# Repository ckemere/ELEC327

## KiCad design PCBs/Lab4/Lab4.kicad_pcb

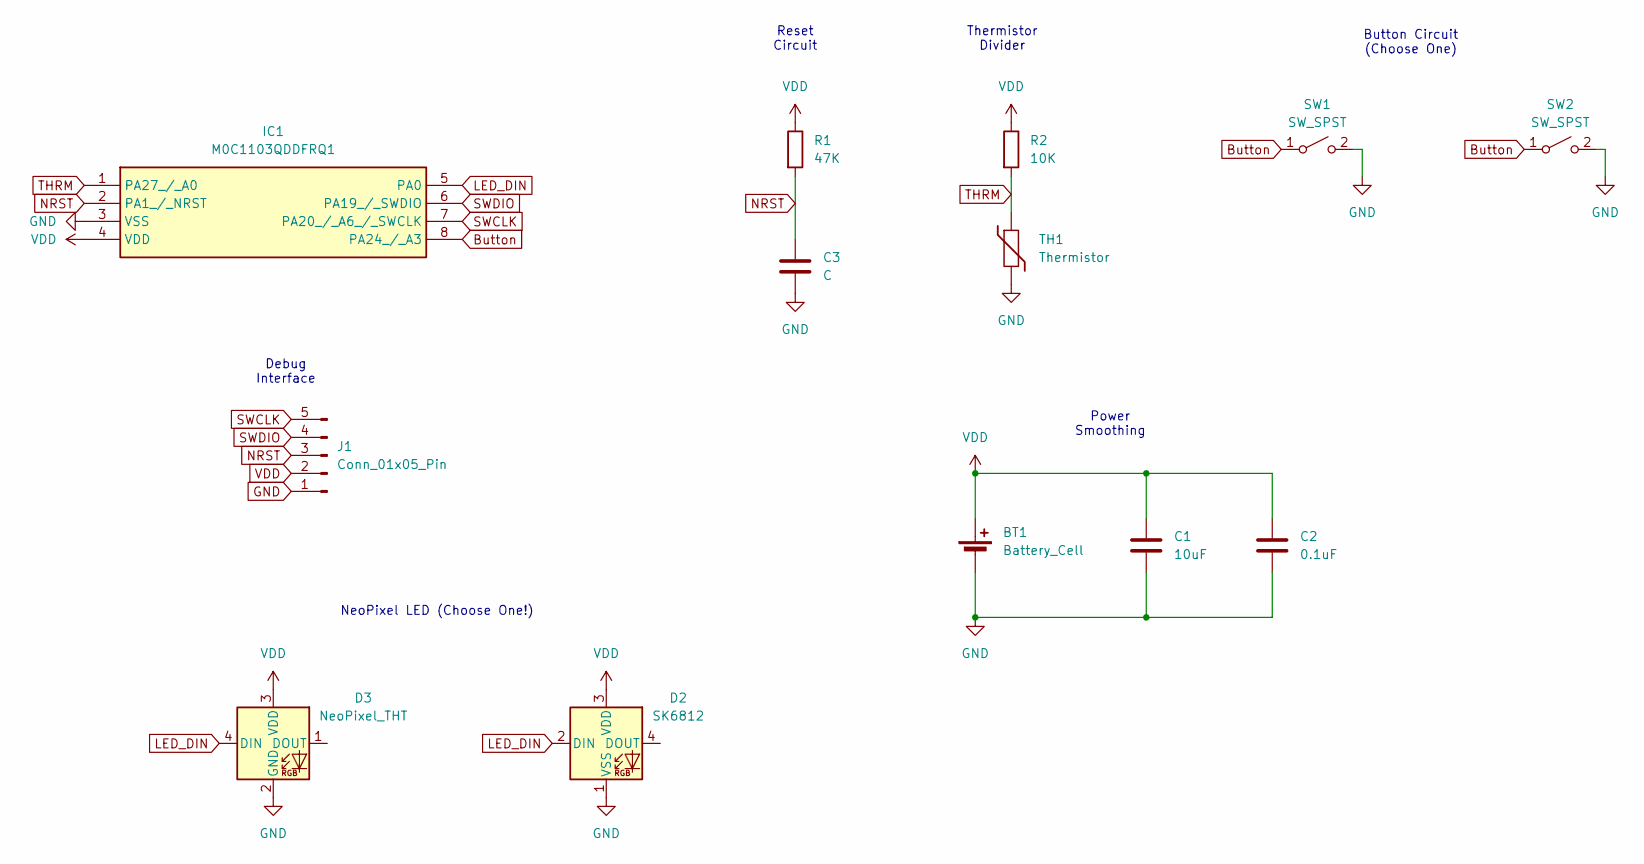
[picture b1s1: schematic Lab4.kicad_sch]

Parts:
BT1: Battery_Cell; BatteryHolder_Keystone_3001_1x12mm
C1: 10uF; C_1206_3216Metric_Pad1.33x1.80mm_HandSolder
C2: 0.1uF; C_1206_3216Metric_Pad1.33x1.80mm_HandSolder
C3: C; C_1206_3216Metric_Pad1.33x1.80mm_HandSolder
D2: SK6812; LED_SK6812_PLCC4_5.0x5.0mm_P3.2mm
D3: NeoPixel_THT; LED_D5.0mm-4_RGB_Staggered_Pins
IC1: M0C1103QDDFRQ1; SOT-23-8; Mouser Part Number 595-M0C1103QDDFRQ1
J1: Conn_01x05_Pin; PinHeader_1x05_P2.54mm_Vertical
R1: 47K; R_1206_3216Metric_Pad1.30x1.75mm_HandSolder
R2: 10K; R_1206_3216Metric_Pad1.30x1.75mm_HandSolder
SW1: SW_SPST; SW_PUSH_6mm_H5mm
SW2: SW_SPST; SW_SPST_PTS647_Sx50
TH1: Thermistor; R_1206_3216Metric_Pad1.30x1.75mm_HandSolder

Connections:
Button: IC1.8 (PA24_/_A3), SW1.1 (A), SW2.1 (A)
GND: BT1.2 (-), C1.2, C2.2, C3.2, D2.1 (VSS), D3.2 (GND), IC1.3 (VSS), J1.1, SW1.2 (B), SW2.2 (B), TH1.2
LED_DIN: D2.2 (DIN), D3.4 (DIN), IC1.5 (PA0)
NRST: C3.1, IC1.2 (PA1_/_NRST), J1.3, R1.2
SWCLK: IC1.7 (PA20_/_A6_/_SWCLK), J1.5
SWDIO: IC1.6 (PA19_/_SWDIO), J1.4
THRM: IC1.1 (PA27_/_A0), R2.2, TH1.1
VDD: BT1.1 (+), C1.1, C2.1, D2.3 (VDD), D3.3 (VDD), IC1.4 (VDD), J1.2, R1.1, R2.1

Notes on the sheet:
Reset Circuit
NeoPixel LED (Choose One!)
Power Smoothing
Debug Interface
Thermistor Divider
Button Circuit (Choose One)

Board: 2 copper layers, 13 parts (0 on the bottom side), 8 nets, no tracks yet.

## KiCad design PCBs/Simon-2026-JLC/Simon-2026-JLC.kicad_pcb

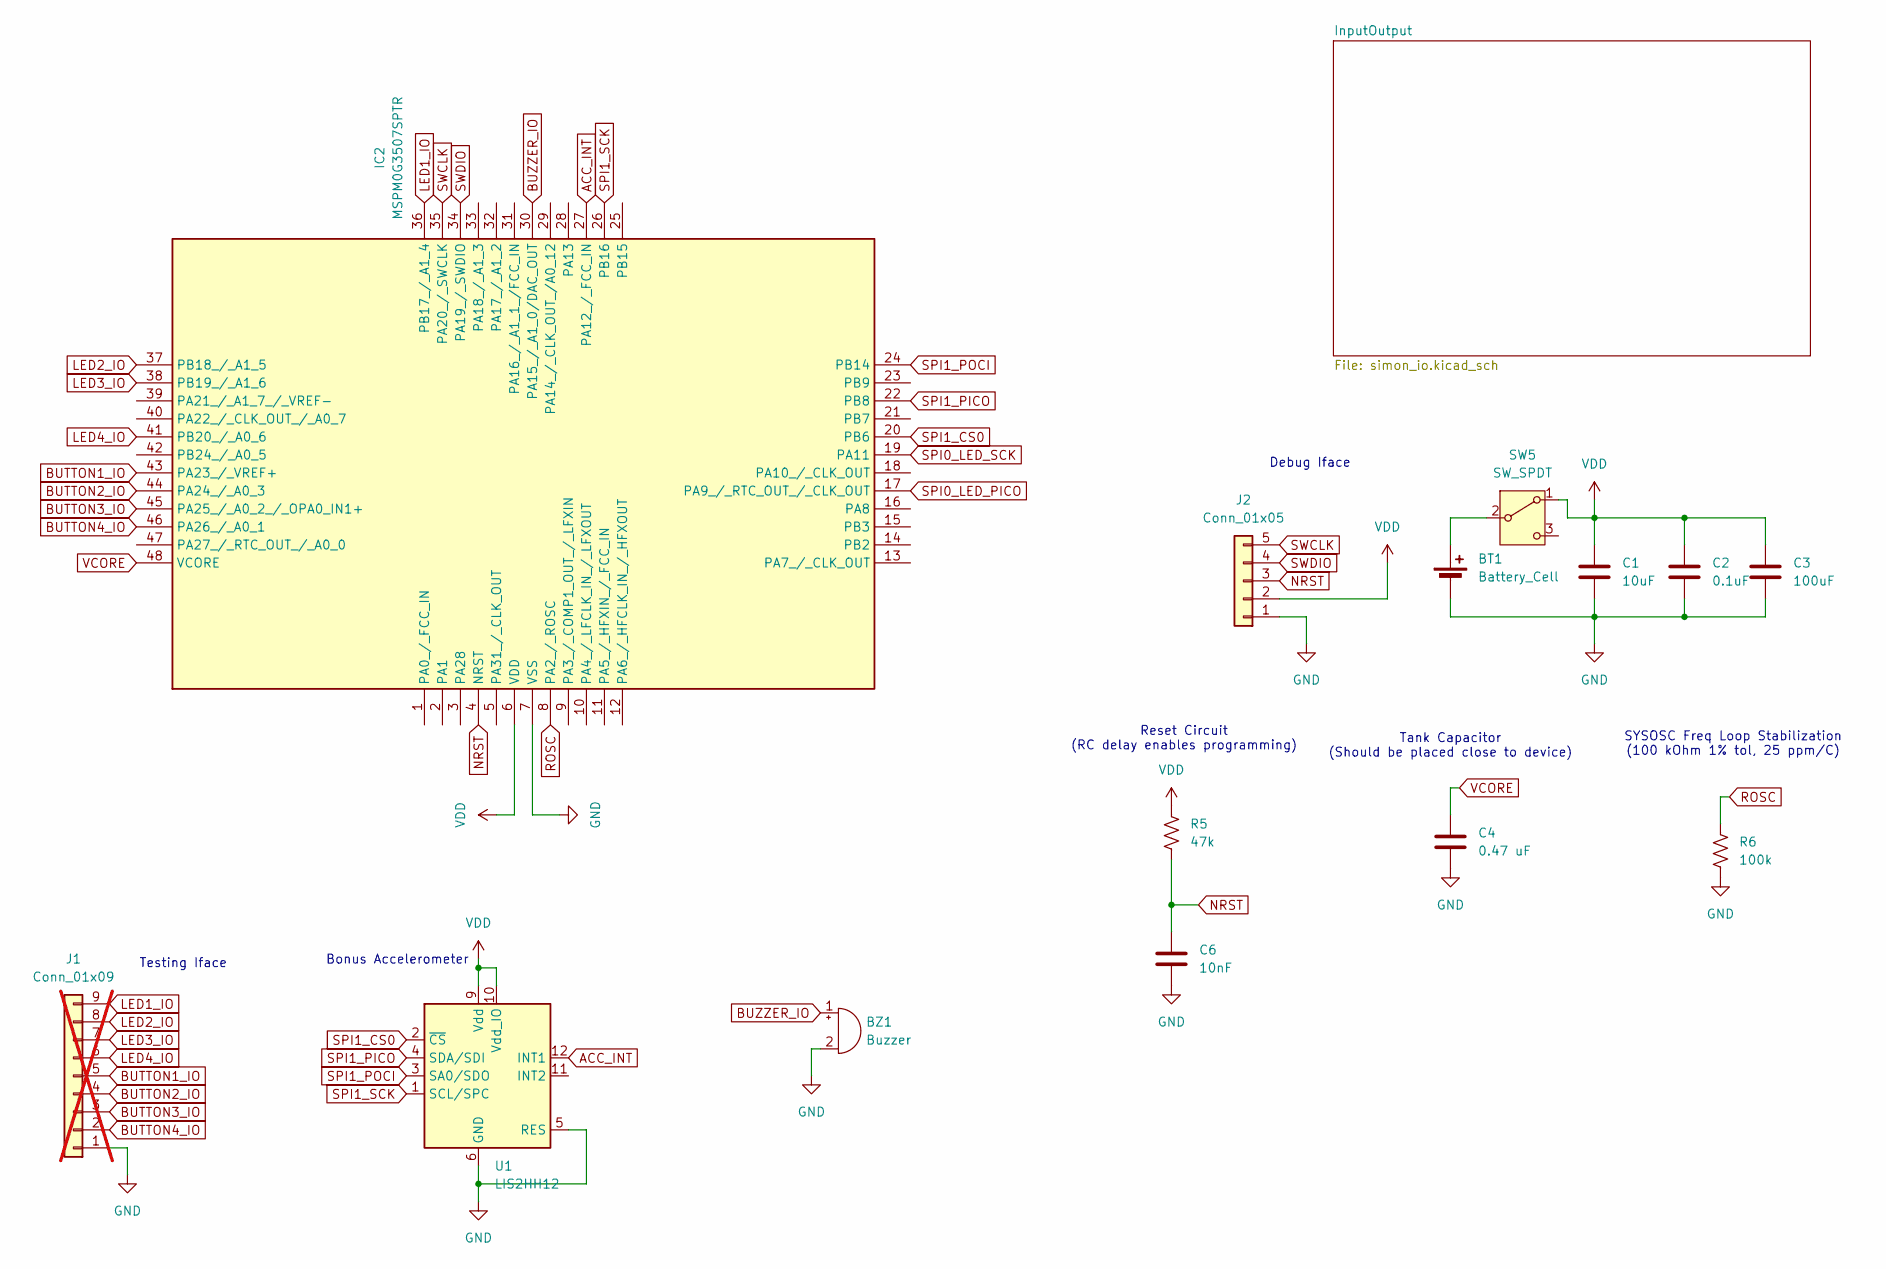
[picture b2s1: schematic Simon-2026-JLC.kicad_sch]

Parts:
BT1: Battery_Cell; BatteryHolder_Keystone_1060_1x2032; MPN C7498148; LCSC Part # C7498148
BZ1: Buzzer; Buzzer_Murata_PKLCS1212E; LCSC Part # C113159
C1: 10uF; C_0603_1608Metric; LCSC Part # C19702
C2: 0.1uF; C_0603_1608Metric_Pad1.08x0.95mm_HandSolder; LCSC Part # C1591
C3: 100uF; C_1206_3216Metric; LCSC Part # C15008
C4: 0.47 uF; C_0805_2012Metric; LCSC Part # C13967
C6: 10nF; C_0402_1005Metric; LCSC Part # C15195
IC2: MSPM0G3507SPTR; QFP50P900X900X160-48N; Mouser Part Number 595-MSPM0G3507SPTR
J1: Conn_01x09; PinHeader_1x09_P2.54mm_Horizontal; not fitted
J2: Conn_01x05; PinHeader_1x05_P2.54mm_Horizontal; LCSC Part # C492413
R5: 47k; R_0603_1608Metric; LCSC Part # C105579
R6: 100k; R_0402_1005Metric; LCSC Part # C60491
SW5: SW_SPDT; SW_EG1270; MPN C20611678; LCSC Part # C20611678
U1: LIS2HH12; LGA-12_2x2mm_P0.5mm; LCSC Part # C221446

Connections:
ACC_INT: IC2.27 (PA12_/_FCC_IN), U1.12 (INT1)
BUTTON1_IO: IC2.43 (PA23_/_VREF+), J1.5; also elsewhere on the board
BUTTON2_IO: IC2.44 (PA24_/_A0_3), J1.4; also elsewhere on the board
BUTTON3_IO: IC2.45 (PA25_/_A0_2_/_OPA0_IN1+), J1.3; also elsewhere on the board
BUTTON4_IO: IC2.46 (PA26_/_A0_1), J1.2; also elsewhere on the board
BUZZER_IO: BZ1.1 (+), IC2.30 (PA15_/_A1_0/DAC_OUT)
GND: BT1.2 (-), BZ1.2 (-), C1.2, C2.2, C3.2, C4.2, C6.2, IC2.7 (VSS), J1.1, J2.1, R6.1, U1.5 (RES), U1.6 (GND), U1.7 (GND), U1.8 (GND); also elsewhere on the board
LED1_IO: IC2.36 (PB17_/_A1_4), J1.9
LED2_IO: IC2.37 (PB18_/_A1_5), J1.8
LED3_IO: IC2.38 (PB19_/_A1_6), J1.7
LED4_IO: IC2.41 (PB20_/_A0_6), J1.6
NRST: C6.1, IC2.4 (NRST), J2.3, R5.1
unnamed: BT1.1 (+), SW5.2 (B)
ROSC: IC2.8 (PA2_/_ROSC), R6.2
SPI0_LED_PICO: IC2.17 (PA9_/_RTC_OUT_/_CLK_OUT); also elsewhere on the board
SPI0_LED_SCK: IC2.19 (PA11); also elsewhere on the board
SPI1_CS0: IC2.20 (PB6), U1.2 (~CS)
SPI1_PICO: IC2.22 (PB8), U1.4 (SDA/SDI)
SPI1_POCI: IC2.24 (PB14), U1.3 (SA0/SDO)
SPI1_SCK: IC2.26 (PB16), U1.1 (SCL/SPC)
SWCLK: IC2.35 (PA20_/_SWCLK), J2.5
SWDIO: IC2.34 (PA19_/_SWDIO), J2.4
VCORE: C4.1, IC2.48 (VCORE)
VDD: C1.1, C2.1, C3.1, IC2.6 (VDD), J2.2, R5.2, SW5.1 (A), U1.9 (Vdd), U1.10 (Vdd_IO); also elsewhere on the board

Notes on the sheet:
Tank Capacitor (Should be placed close to device)
Reset Circuit (RC delay enables programming)
Debug Iface
Testing Iface
Bonus Accelerometer
SYSOSC Freq Loop Stabilization (100 kOhm 1% tol, 25 ppm/C)

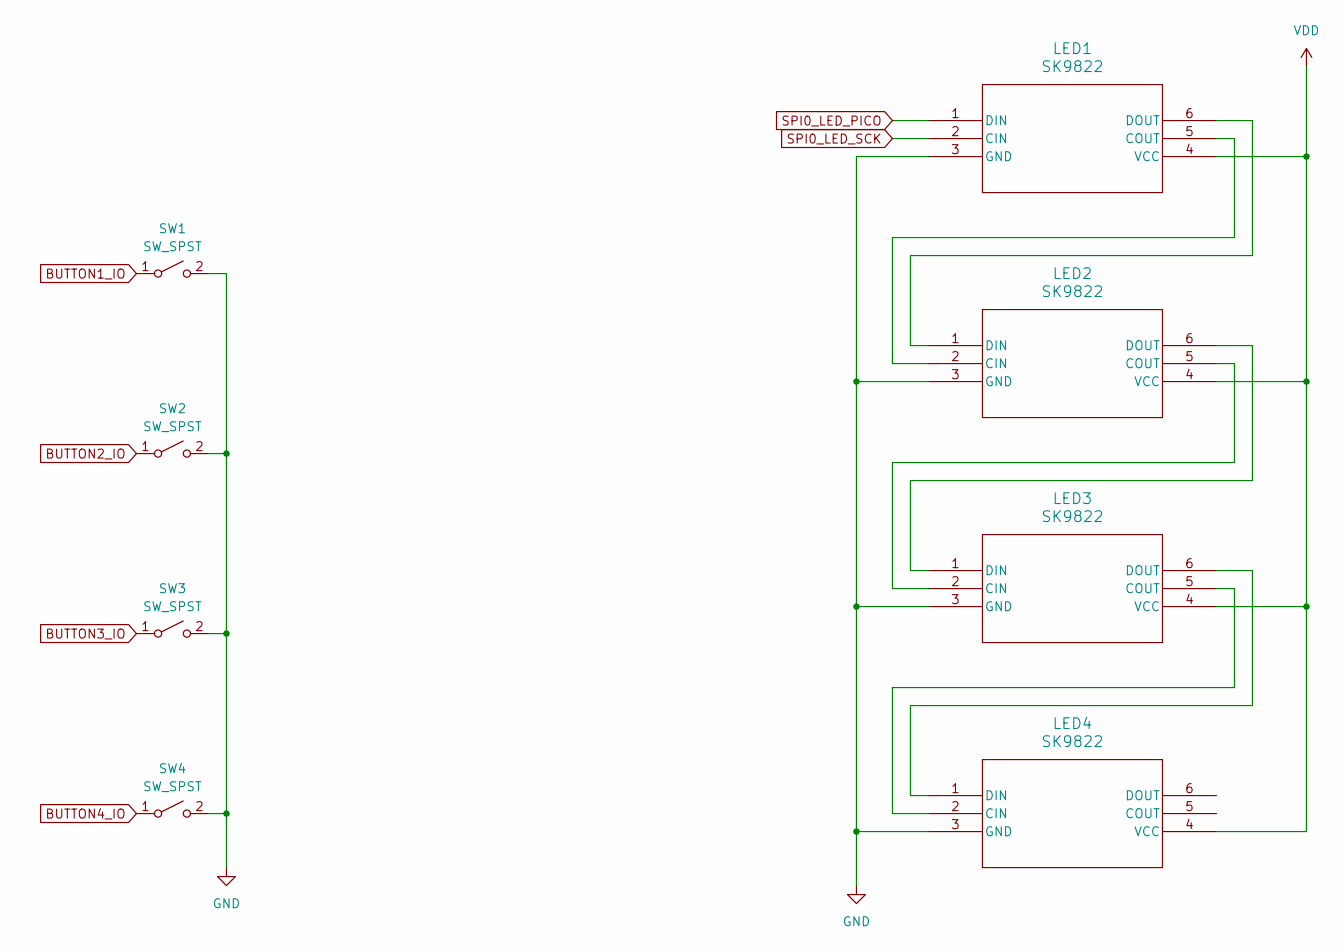
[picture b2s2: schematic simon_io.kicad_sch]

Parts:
LED1, LED2, LED3, LED4: SK9822; LED_RGB_5050-6; LCSC Part # C2829089
SW1, SW2, SW3, SW4: SW_SPST; SW_SPST_PTS647_Sx38; MPN C2799279; LCSC Part # C2799279

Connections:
BUTTON1_IO: SW1.1 (A); also elsewhere on the board
BUTTON2_IO: SW2.1 (A); also elsewhere on the board
BUTTON3_IO: SW3.1 (A); also elsewhere on the board
BUTTON4_IO: SW4.1 (A); also elsewhere on the board
GND: LED1.3 (GND), LED2.3 (GND), LED3.3 (GND), LED4.3 (GND), SW1.2 (B), SW2.2 (B), SW3.2 (B), SW4.2 (B); also elsewhere on the board
unnamed: LED1.5 (COUT), LED2.2 (CIN)
unnamed: LED1.6 (DOUT), LED2.1 (DIN)
unnamed: LED2.5 (COUT), LED3.2 (CIN)
unnamed: LED2.6 (DOUT), LED3.1 (DIN)
unnamed: LED3.5 (COUT), LED4.2 (CIN)
unnamed: LED3.6 (DOUT), LED4.1 (DIN)
SPI0_LED_PICO: LED1.1 (DIN); also elsewhere on the board
SPI0_LED_SCK: LED1.2 (CIN); also elsewhere on the board
VDD: LED1.4 (VCC), LED2.4 (VCC), LED3.4 (VCC), LED4.4 (VCC); also elsewhere on the board

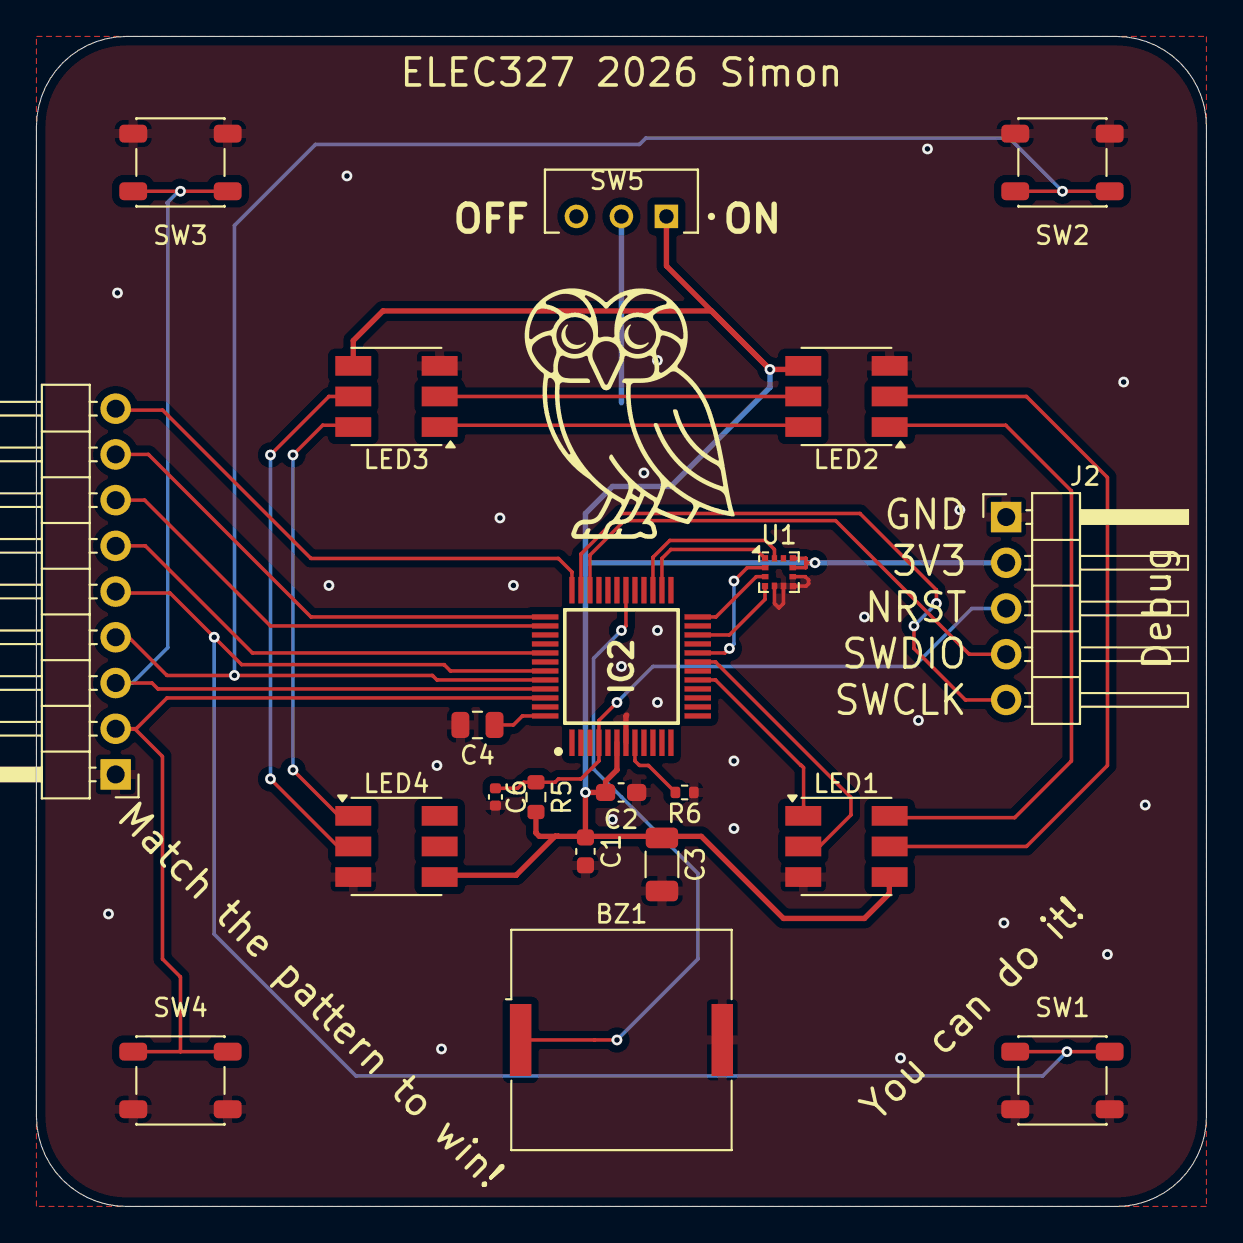
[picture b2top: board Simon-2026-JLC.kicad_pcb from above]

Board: 2 copper layers, 65.0 x 65.0 mm, 22 parts (1 on the bottom side), 30 nets.

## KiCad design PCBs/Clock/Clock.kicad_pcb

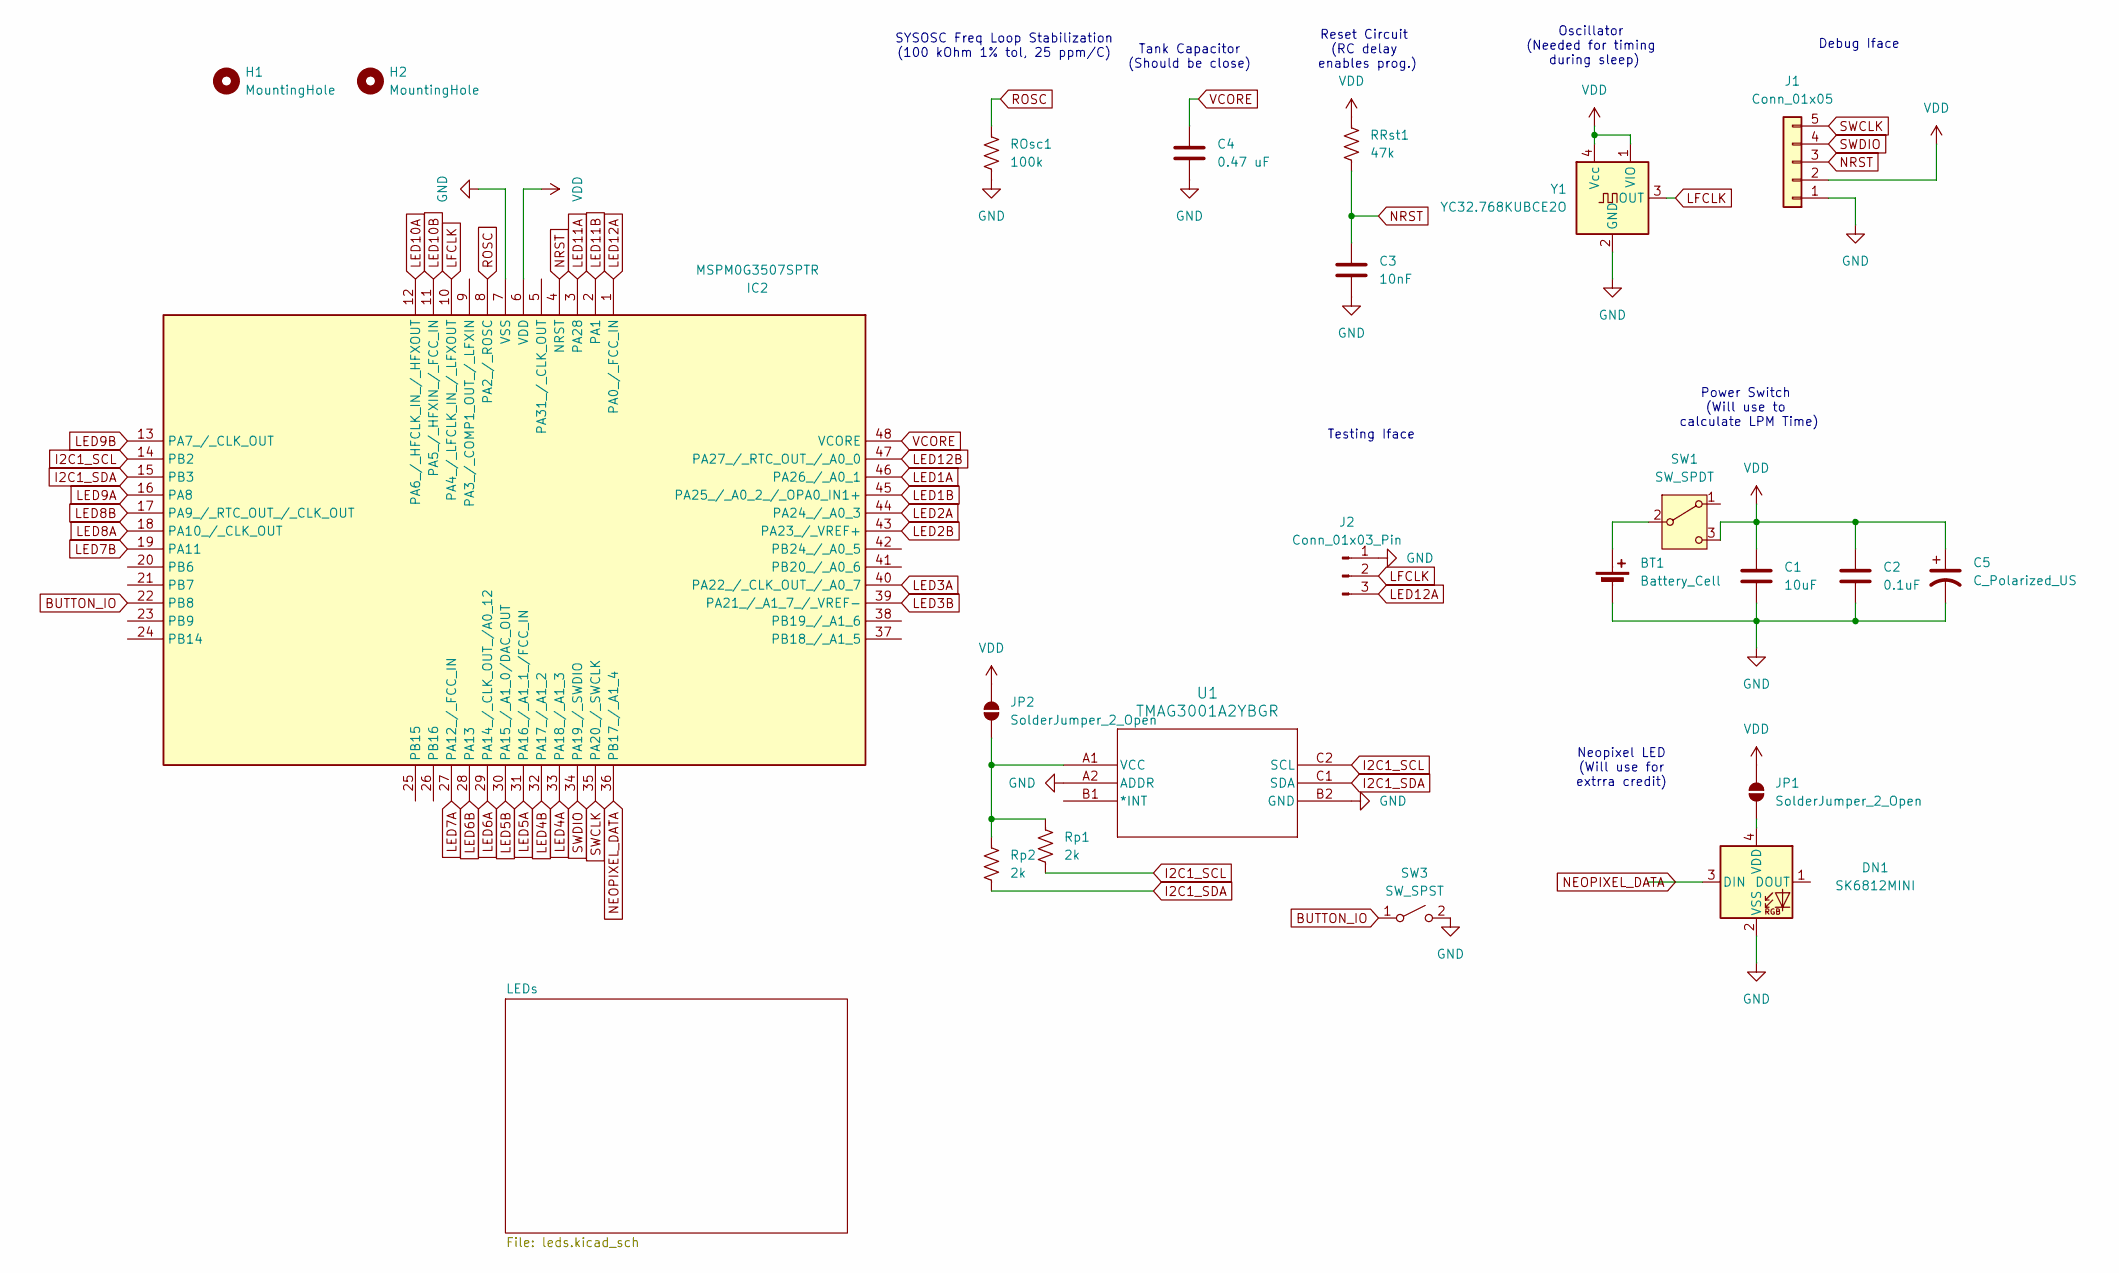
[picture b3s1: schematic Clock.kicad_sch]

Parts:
BT1: Battery_Cell; BatteryHolder_Keystone_1060_1x2032; MPN C7498148
C1: 10uF; C_1206_3216Metric_Pad1.33x1.80mm_HandSolder
C2: 0.1uF; C_0603_1608Metric_Pad1.08x0.95mm_HandSolder
C3: 10nF; C_0402_1005Metric
C4: 0.47 uF; C_0603_1608Metric_Pad1.08x0.95mm_HandSolder
C5: C_Polarized_US; CP_Radial_D8.0mm_P3.50mm
DN1: SK6812MINI; LED_SK6812MINI_PLCC4_3.5x3.5mm_P1.75mm; MPN C2886570
H1, H2: MountingHole; MountingHole_2.1mm
IC2: MSPM0G3507SPTR; LQFP-48_7x7mm_P0.5mm; Mouser Part Number 595-MSPM0G3507SPTR
J1: Conn_01x05; PinHeader_1x05_P2.54mm_Horizontal; MPN C492413
J2: Conn_01x03_Pin; PinHeader_1x03_P2.54mm_Horizontal; MPN C42431830
JP1, JP2: SolderJumper_2_Open; SolderJumper-2_P1.3mm_Open_TrianglePad1.0x1.5mm
ROsc1: 100k; R_0402_1005Metric
RRst1: 47k; R_0402_1005Metric
Rp1, Rp2: 2k; R_0402_1005Metric
SW1: SW_SPDT; SW_EG1270; MPN C20611678
SW3: SW_SPST; SW_SPST_PTS647_Sx38; MPN C2799279
U1: TMAG3001A2YBGR; DSBGA6_YBG_TEX; MPN C31115089
Y1: YC32.768KUBCE2O; Crystal_SMD_3225-4Pin_3.2x2.5mm; MPN C52204803

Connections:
BUTTON_IO: IC2.22 (PB8), SW3.1 (A)
GND: BT1.2 (-), C1.2, C2.2, C3.2, C4.2, C5.2, DN1.2 (VSS), IC2.7 (VSS), J1.1, J2.1, ROsc1.1, SW3.2 (B), U1.A2 (ADDR), U1.B2 (GND), Y1.2 (GND)
I2C1_SCL: IC2.14 (PB2), Rp1.1, U1.C2 (SCL)
I2C1_SDA: IC2.15 (PB3), Rp2.1, U1.C1 (SDA)
LED1A: IC2.46 (PA26_/_A0_1); also elsewhere on the board
LED1B: IC2.45 (PA25_/_A0_2_/_OPA0_IN1+); also elsewhere on the board
LED2A: IC2.44 (PA24_/_A0_3); also elsewhere on the board
LED2B: IC2.43 (PA23_/_VREF+); also elsewhere on the board
LED3A: IC2.40 (PA22_/_CLK_OUT_/_A0_7); also elsewhere on the board
LED3B: IC2.39 (PA21_/_A1_7_/_VREF-); also elsewhere on the board
LED4A: IC2.33 (PA18_/_A1_3); also elsewhere on the board
LED4B: IC2.32 (PA17_/_A1_2); also elsewhere on the board
LED5A: IC2.31 (PA16_/_A1_1_/FCC_IN); also elsewhere on the board
LED5B: IC2.30 (PA15_/_A1_0/DAC_OUT); also elsewhere on the board
LED6A: IC2.29 (PA14_/_CLK_OUT_/A0_12); also elsewhere on the board
LED6B: IC2.28 (PA13); also elsewhere on the board
LED7A: IC2.27 (PA12_/_FCC_IN); also elsewhere on the board
LED7B: IC2.19 (PA11); also elsewhere on the board
LED8A: IC2.18 (PA10_/_CLK_OUT); also elsewhere on the board
LED8B: IC2.17 (PA9_/_RTC_OUT_/_CLK_OUT); also elsewhere on the board
LED9A: IC2.16 (PA8); also elsewhere on the board
LED9B: IC2.13 (PA7_/_CLK_OUT); also elsewhere on the board
LED10A: IC2.12 (PA6_/_HFCLK_IN_/_HFXOUT); also elsewhere on the board
LED10B: IC2.11 (PA5_/_HFXIN_/_FCC_IN); also elsewhere on the board
LED11A: IC2.3 (PA28); also elsewhere on the board
LED11B: IC2.2 (PA1); also elsewhere on the board
LED12A: IC2.1 (PA0_/_FCC_IN), J2.3; also elsewhere on the board
LED12B: IC2.47 (PA27_/_RTC_OUT_/_A0_0); also elsewhere on the board
LFCLK: IC2.10 (PA4_/_LFCLK_IN_/_LFXOUT), J2.2, Y1.3 (OUT)
NEOPIXEL_DATA: DN1.3 (DIN), IC2.36 (PB17_/_A1_4)
NRST: C3.1, IC2.4 (NRST), J1.3, RRst1.1
unnamed: BT1.1 (+), SW1.2 (B)
unnamed: DN1.4 (VDD), JP1.1 (A)
unnamed: JP2.1 (A), Rp1.2, Rp2.2, U1.A1 (VCC)
ROSC: IC2.8 (PA2_/_ROSC), ROsc1.2
SWCLK: IC2.35 (PA20_/_SWCLK), J1.5
SWDIO: IC2.34 (PA19_/_SWDIO), J1.4
VCORE: C4.1, IC2.48 (VCORE)
VDD: C1.1, C2.1, C5.1, IC2.6 (VDD), J1.2, JP1.2 (B), JP2.2 (B), RRst1.2, SW1.3 (C), Y1.1 (VIO), Y1.4 (Vcc); also elsewhere on the board

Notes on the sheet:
Tank Capacitor (Should be close)
Oscillator (Needed for timing during sleep)
Reset Circuit (RC delay enables prog.)
Power Switch (Will use to calculate LPM Time)
Debug Iface
Testing Iface
SYSOSC Freq Loop Stabilization (100 kOhm 1% tol, 25 ppm/C)
Neopixel LED (Will use for extrra credit)

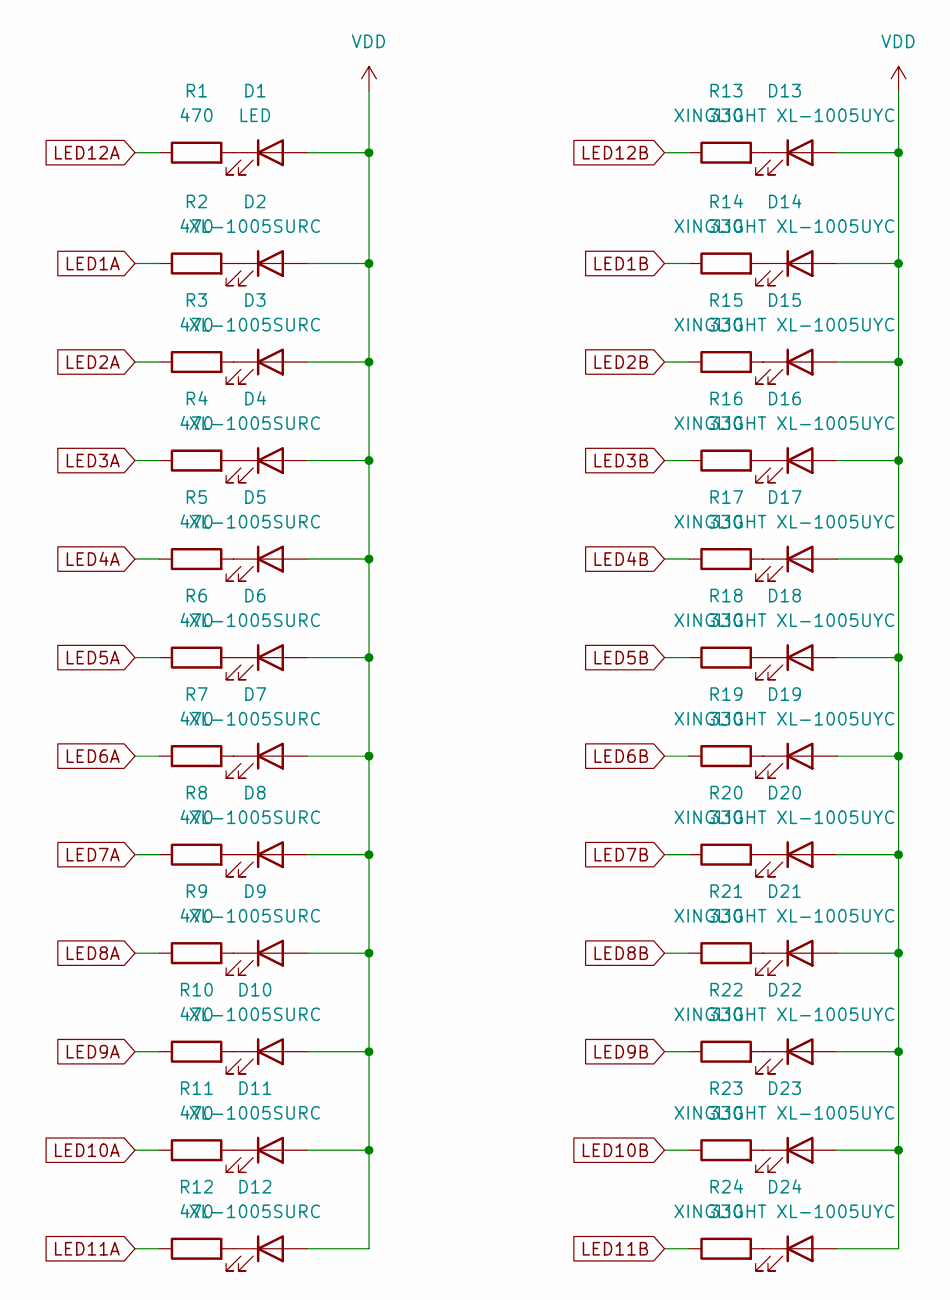
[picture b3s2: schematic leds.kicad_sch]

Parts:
D1: LED; LED_0603_1608Metric; MPN C19171390
D2, D3, D4, D5, D6, D7, D8, D9, D10, D11, D12: XL-1005SURC; LED_0402_1005Metric; MPN C25503345
D13, D14, D15, D16, D17, D18, D19, D20, D21, D22, D23, D24: XINGLIGHT XL-1005UYC; LED_0402_1005Metric; MPN C25503856
R1, R2, R3, R4, R5, R6, R7, R8, R9, R10, R11, R12: 470; R_0402_1005Metric
R13, R14, R15, R16, R17, R18, R19, R20, R21, R22, R23, R24: 330; R_0402_1005Metric

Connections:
LED1A: R2.1; also elsewhere on the board
LED1B: R14.1; also elsewhere on the board
LED2A: R3.1; also elsewhere on the board
LED2B: R15.1; also elsewhere on the board
LED3A: R4.1; also elsewhere on the board
LED3B: R16.1; also elsewhere on the board
LED4A: R5.1; also elsewhere on the board
LED4B: R17.1; also elsewhere on the board
LED5A: R6.1; also elsewhere on the board
LED5B: R18.1; also elsewhere on the board
LED6A: R7.1; also elsewhere on the board
LED6B: R19.1; also elsewhere on the board
LED7A: R8.1; also elsewhere on the board
LED7B: R20.1; also elsewhere on the board
LED8A: R9.1; also elsewhere on the board
LED8B: R21.1; also elsewhere on the board
LED9A: R10.1; also elsewhere on the board
LED9B: R22.1; also elsewhere on the board
LED10A: R11.1; also elsewhere on the board
LED10B: R23.1; also elsewhere on the board
LED11A: R12.1; also elsewhere on the board
LED11B: R24.1; also elsewhere on the board
LED12A: R1.1; also elsewhere on the board
LED12B: R13.1; also elsewhere on the board
unnamed: D1.1 (K), R1.2
unnamed: D2.1 (K), R2.2
unnamed: D3.1 (K), R3.2
unnamed: D4.1 (K), R4.2
unnamed: D5.1 (K), R5.2
unnamed: D6.1 (K), R6.2
unnamed: D7.1 (K), R7.2
unnamed: D8.1 (K), R8.2
unnamed: D9.1 (K), R9.2
unnamed: D10.1 (K), R10.2
unnamed: D11.1 (K), R11.2
unnamed: D12.1 (K), R12.2
unnamed: D13.1 (K), R13.2
unnamed: D14.1 (K), R14.2
unnamed: D15.1 (K), R15.2
unnamed: D16.1 (K), R16.2
unnamed: D17.1 (K), R17.2
unnamed: D18.1 (K), R18.2
unnamed: D19.1 (K), R19.2
unnamed: D20.1 (K), R20.2
unnamed: D21.1 (K), R21.2
unnamed: D22.1 (K), R22.2
unnamed: D23.1 (K), R23.2
unnamed: D24.1 (K), R24.2
VDD: D1.2 (A), D2.2 (A), D3.2 (A), D4.2 (A), D5.2 (A), D6.2 (A), D7.2 (A), D8.2 (A), D9.2 (A), D10.2 (A), D11.2 (A), D12.2 (A), D13.2 (A), D14.2 (A), D15.2 (A), D16.2 (A), D17.2 (A), D18.2 (A), D19.2 (A), D20.2 (A), D21.2 (A), D22.2 (A), D23.2 (A), D24.2 (A); also elsewhere on the board

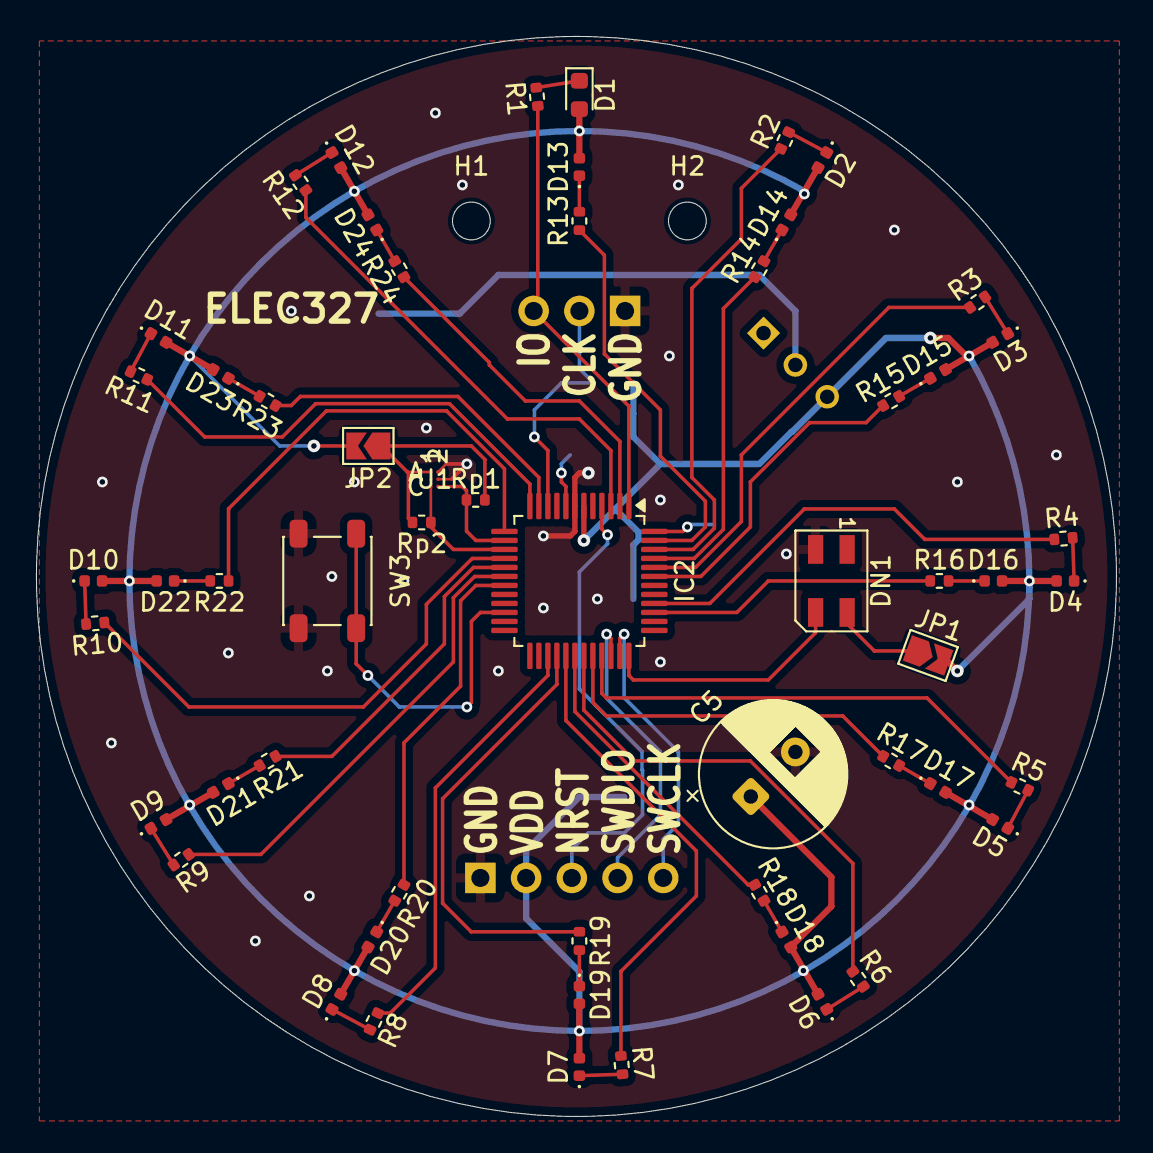
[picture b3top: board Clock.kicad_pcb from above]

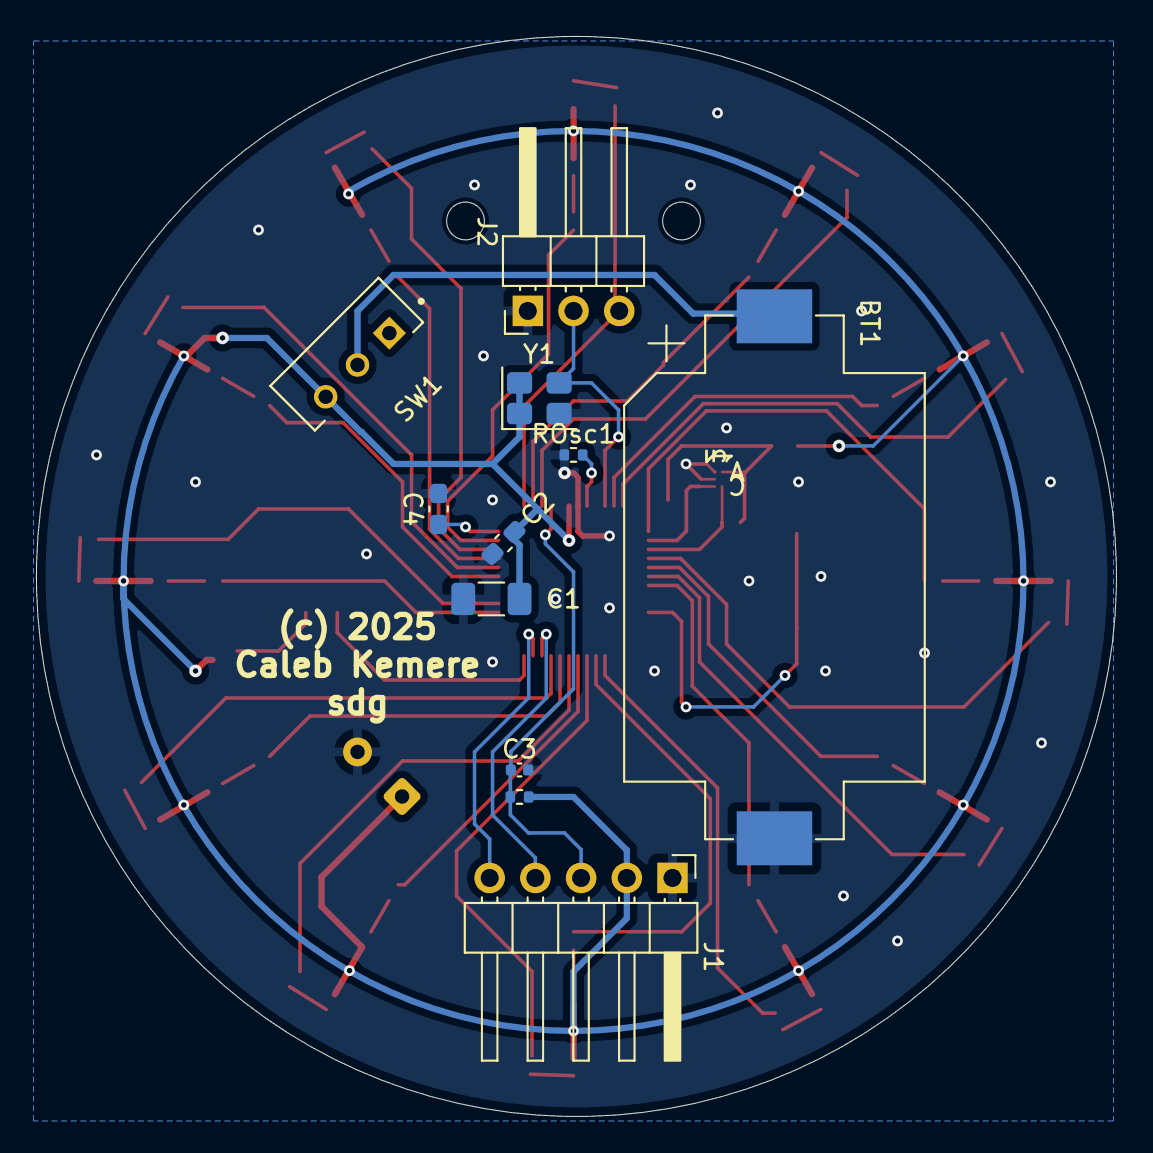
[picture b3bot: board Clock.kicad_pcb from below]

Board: 2 copper layers, 60.0 x 60.0 mm, 70 parts (11 on the bottom side), 63 nets.

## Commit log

2014-01-29 Mood ring PCB updated.
2014-01-29 Mood ring PCB updated (for real this time).
2014-01-30 Added DRC and DRU files
2014-01-31 Added Lab 2 library file
2014-02-10 Added novel CR2032 battery clip.
2015-01-30 Added data sheets and docs for MSP430s and Battery Holders
2015-01-30 Updated skeleton file for lab 2 and updated library
2015-02-02 added gitignore
2015-02-02 updated documents and added gitignore
2015-02-02 Changed MSP430 part from through-hole to SMD
2015-03-17 Added Lab 6 schematic
2015-03-17 Fixed buzzer connections
2015-03-17 added lab 2
2015-03-19 Switched to Xin Huang's schematic
2015-03-25 Changed dru file top properly generate EXCELLON_24 drill files rather than old EXCELLON
2015-03-25 Fixed VCC bug
2016-02-05 Added Labs directory, changed Lab2 to Lab3 and added datasheets
2016-02-07 Moved lab3_skeleton.c to this reposistory
2016-02-10 Added code examples and moved datasheet
2016-02-21 Moved Simon schematic to Midterm directory
2016-10-03 Added Simon schematic and board files
2016-12-28 Updated gitignore and added Pendant from 2016
2016-12-28 Updated pendant to 2017 version
2017-02-06 Updated data sheets
2017-03-16 Updated directory structure
2018-01-12 Added lab1 code
2018-01-12 Updated Pendant Eagle files
2018-01-14 Updated example file with comments
2018-01-18 Updated pendant code.
2018-01-18 Updated pendant skeleton code
2018-01-18 Updated to make epsilon harder
2018-01-21 Updated location of Pendant schematic and board files
2018-01-21 Added Bonus schematic and board files
2018-01-30 Update Lab 3 skeleton
2018-01-31 Update lab3 skeleton code to properly source ACLK from VLO
2018-02-02 Added datasheets for PCB parts
2018-02-02 Remove old unnecessary Lab 3 datasheets
2018-02-08 Added resistor for reset pin
2018-12-10 Fixed bug in bonus PCB
2018-12-10 Updated LED resistors from 1K to 300 ohms
2019-01-30 Moved Lab3 to Lab4 and added new RGB LED. Also updated Bonus PCB for manufacturing
2019-01-30 Removed old RGB LED
2019-01-30 Added back lab 3 directory and skeleton code!
2019-02-11 Updated and changed the name of CAM file. Added panelization scripts.
2019-03-15 Add updated design rules file with safer clearances to avoid pcb issues
2019-03-15 Update EAGLE library with support for MSP430 32 pin QFN package
2019-04-19 Added MSP430G2ET Launchpad app note
2019-04-19 Remove thermal vias due to massive amount of issues they cause
2019-12-31 Updated Pendant design for 2019
2020-01-23 Updated pendant.c initial template.
2020-01-31 Updated pendant template code to have LPM4 button
2020-02-06 Updated Lab 4 RGB led part
2020-03-13 Added a smd switch
2020-03-16 Added design for 2020 mailout
2020-03-17 Added holes in soldermask for stencil alignment.
2020-03-22 Added firmware for PCBs that are being sent out for 2020.
2020-04-13 Added sample code to adjust RGB LEDs based on temperature.
2020-04-16 Updated Lab 9 code to fix bug
2020-05-05 Added Simon 2020 programs
2020-05-05 Updated README for contestant E
2020-12-30 Updated pendant for 2021 (tic tac toe)
2021-01-13 Saved 2020 version of Lab2 Pendant in a new directory
2021-02-02 Updated lab1 skeleton codes for 2021
2021-02-23 Restored original 2020 pendant in directory, made a new directory for 2021 fabbed pendant, and a directory for Bonus PCB.
2021-02-24 Updates for 2021, including design for the Aisler panel for fab and giveaway.
2021-03-07 Added first bit of parsing for Panelizer
2021-03-08 Updated scripts for panelization. Now also doing stuff with GerberTools Panelizer.
2021-03-08 Updated to work properly with shifted, rotated boards.
2021-03-08 One more update to panelizer to try to deal with gergmerge repeating placements. Doesn't work, unfortunately.
2021-03-09 Added directory of temperature ADC examples.
2021-12-20 Pendant for 2022 is a 5x7 LED array
2022-01-07 Added stuff for Lab 2 PCB handout
2022-01-07 Updated panelizing script - new eagle version
2022-01-26 2021 lab structure
2022-01-27 Updated 2022 Lab 3
2022-02-07 Added accelerometer schematic for 2022
2022-02-07 Fixed connections in Lab 4 schematic
2022-02-11 Updates for Lab 5
2022-02-11 Added a few comments
2022-02-21 Added 2022 Simon board.
2022-02-21 Delete SimonPCBTest.ino
    Get rid of temptation to use Energia
2022-03-09 Added some helper code for Simon
2022-03-09 Fixed bugs in Simon template code
2022-03-09 Updated simon code
2023-01-09 2023 updates
2023-01-09 2023-Updates 2 - midterm project and libraries
2023-01-10 Added FR2433 documents
2023-01-17 Updated Lab to MSP430FR2433
2023-01-17 Update skeleton ver 1 to MSP430FR2443
2023-01-17 Update skeleton ver 2 to MSP430FR2443
2023-01-23 Updated lab1 with fix for 2023
2023-01-23 Restored scarlett's pushes
2023-01-23 And ver2 for 2023
2023-01-24 Updated for 2023
2023-01-24 Fixed #ifdef to refer to a proper label - #ifdef __MSP430FR2XX_4XX_FAMILY__
2023-02-08 Added different variant MSP430 and programming header and 1632 battery holder.
2023-02-11 Added RGB LED to library
2023-02-11 Added datasheets for parts
2023-02-16 Small update main.c
2023-02-20 Updated Numbers.c in Lab 5
2023-04-24 Added FR examples
2025-01-15 Adding stuff before switch over to M0+
2025-01-15 2024 switch to MSPM0+
2025-01-15 Purged old files
2025-01-15 Update make file to check for header dependencies and removed some spaces in code file
2025-01-15 Updated blink Makefile and code to reference a standard c and header file for class
2025-01-18 Updated docs
2025-01-21 Added code to measure pulse widths using another Launchpad
2025-01-21 Update pulsewidth measuring code to higher accuracy ROSC
2025-01-21 Updates to documentation
2025-01-21 Added Lab2 python interfacing code
2025-01-26 Updates to pulsewidth measuring program. Updated baudrate to 921600. Also measure space before pulse
2025-01-27 BufferedPulseWidth code added. (We'll remove it later.)
2025-01-27 Updated buffered. Will delete later
2025-01-27 Clocked version of code
2025-01-27 Removed buffered and original timed code
2025-01-27 Added pulsewidth binary
2025-01-27 Added a test code binary for pulsewidth
2025-01-30 Added two launchpad configuration with serial numbers
2025-01-30 Updated ClockedPulsewidth measurement. We now will assert PB6 to a 0 whenever the character 'r' is received. Connect this pin to the NRST pin so that we get a defined reset time. Second, we now repor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
2025-01-30 Updated binary
2025-01-30 Lab2 test code added
2025-02-03 Updated read_data.py for ClockedPulseWidth to have command line options
2025-02-03 Update README.md
    fixed link rendering for instruction set
2025-02-05 Added Simon 2025 PCB design
2025-02-05 Added Kicad parts library
2025-02-07 Update read_data.py
    Added a help comment for usage
2025-02-18 Updates to Kicad library for Lab 5
2025-02-21 Updated Simon PCB 2025
2025-03-24 Scripts for panelizing from KiCAD
2025-03-24 Comment for parse_panel_svg
2025-04-15 added JLC version of simon
2025-04-20 Added picture of Fabricated PCB
2025-04-20 Added Lab 5 PCB microcontroller to documents
2025-04-23 Added footprints
2025-04-23 Added LFQP48 pin device
2025-04-28 Updated parse_submissions to optionally take a grade file to gather netids
2025-05-12 Added comments to README about Launchpad serial number. Added reset option to firmware.
2025-11-26 Fixed issue with NRST pullup resistor not being connected
2026-01-12 Added for 2026
2026-01-13 Fixed gitignore for Debug
2026-01-13 Project name to lower case to match directory
2026-01-14 Added a workspace file
2026-01-14 Updated and simplified blink.c code
2026-01-14 Maybe missing dependencies added
2026-01-14 Updated project to most recent clang tools version
2026-01-14 Updated .cproject
2026-01-14 Updated Datasheet and TRM and Errata to latest
2026-01-15 Updated Lab 1 PCB files
2026-01-15 Added Lab 1 template
2026-01-15 PCB gitignore
2026-01-21 Added LED datasheets
2026-01-24 Updates for Lab 2
2026-01-27 Fixed issue with Lab2
2026-01-28 Added more project files
2026-01-28 Updated project files for blink_sleep and blink_standby
2026-02-02 Simon PCB 2026
2026-02-02 Added Simon 2026 gitignore
2026-02-03 Added template for Lab 3
2026-02-09 Updates for PCB design Lab
2026-02-09 Added MSPM0 C series doc
2026-02-09 Updated Lab 4 with connections
2026-02-09 Updated Lab4 PCB with design rules and exclusions
2026-02-11 Fixed missing VDD and GND
2026-02-11 Switched through hole footprint for RGB LED
2026-03-02 Lab 6 workspace
2026-03-12 Added Simon Template
2026-04-22 Updated pin assignments
